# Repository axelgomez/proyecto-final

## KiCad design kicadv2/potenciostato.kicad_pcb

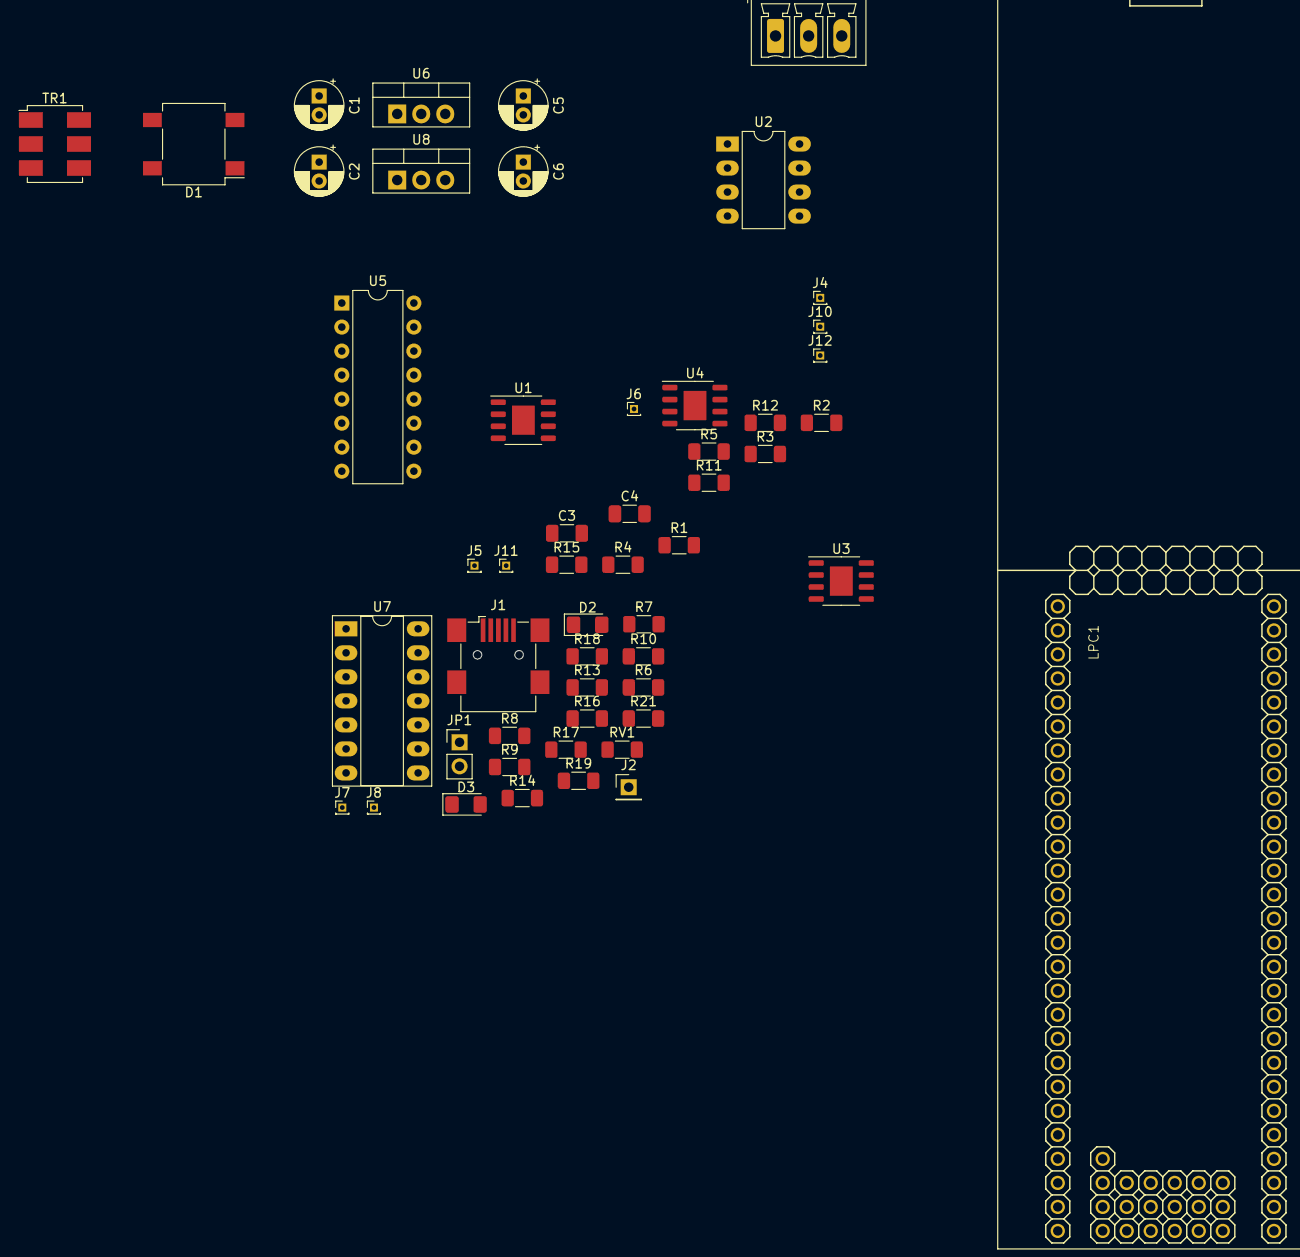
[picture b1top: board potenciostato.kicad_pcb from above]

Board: 2 copper layers, 52 parts (0 on the bottom side), 42 nets, no tracks yet.

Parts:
C1, C2, C5, C6: 10uF; CP_Radial_D5.0mm_P2.00mm
C3, C4: 100nF; C_1206_3216Metric_Pad1.33x1.80mm_HandSolder
D1: D_Bridge_+-AA; Diode_Bridge_Vishay_DFS
D2, D3: 1N4007; D_1206_3216Metric_Pad1.42x1.75mm_HandSolder
J1: USB_B_Micro; USB_Mini-B_Wuerth_65100516121_Horizontal
J2: test_DAC; PinHeader_1x01_P2.54mm_Vertical
J3: Conn_01x03_Male; PhoenixContact_MCV_1,5_3-G-3.5_1x03_P3.50mm_Vertical
J4, J7: test_I; PinHeader_1x01_P1.00mm_Vertical
J5, J8: test_V; PinHeader_1x01_P1.00mm_Vertical
J6: test_DAC; PinHeader_1x01_P1.00mm_Vertical
J10, J11, J12: test_GND; PinHeader_1x01_P1.00mm_Vertical
JP1: alimentacion_lpc; PinHeader_1x02_P2.54mm_Vertical
LPC1: LPCXPRESSO_LPC1769
R1, R10, R21: 1K; R_1206_3216Metric_Pad1.30x1.75mm_HandSolder
R2, R3, R11: 100K; R_1206_3216Metric_Pad1.30x1.75mm_HandSolder
R4, R6, R7, R8, R9, R14, R15, R18: 10K; R_1206_3216Metric_Pad1.30x1.75mm_HandSolder
R5: 6K8; R_1206_3216Metric_Pad1.30x1.75mm_HandSolder
R12, R17: 4K7; R_1206_3216Metric_Pad1.30x1.75mm_HandSolder
R13, R16, R19: 5K6; R_1206_3216Metric_Pad1.30x1.75mm_HandSolder
RV1: 10K; R_1206_3216Metric_Pad1.30x1.75mm_HandSolder
TR1: ADT2-71T; Mini-Circuits_CD637_H5.23mm
U1, U3, U4: OP77; HSOP-8-1EP_3.9x4.9mm_P1.27mm_EP2.41x3.1mm
U2: TL082; DIP-8_W7.62mm_LongPads
U5: 4316; DIP-16_W7.62mm
U6: L7805; TO-220-3_Vertical
U7: TL064; DIP-14_W7.62mm_Socket_LongPads
U8: L7905; TO-220-3_Vertical

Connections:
+5V: C5.1, JP1.1, R16.2, U1.7, U2.8, U3.7, U4.7, U5.16, U6.3, U7.4
-5V: C6.2, U1.4, U2.4, U3.4, U4.4, U5.9, U7.11, U8.3
/salida_dac/I_IN: J4.1, R14.2, U1.6, U5.2, U5.3, U5.11, U5.12
/salida_dac/VIN: J6.1, R2.2, R13.1, U7.1
/salida_dac/VOffset: R7.2, R8.1, R10.1, U7.13, U7.14
/salida_dac/V_IN: J5.1, R21.2, U2.6, U2.7
/salida_dac/gan_x0.1: LPC1.49, U5.15
/salida_dac/gan_x1: LPC1.47, U5.5
/salida_dac/gan_x5: LPC1.48, U5.6
/salida_dac/gan_x10: LPC1.50, U5.14
GND: C1.2, C2.1, C3.2, C4.1, C5.2, C6.1, D3.1, J1.5, J1.6, J10.1, J11.1, J12.1, LPC1.1, LPC1.54, R19.1, TR1.5, U1.3, U3.3, U4.3, U5.7, U5.8, U6.2, U8.1
unnamed: C1.1, C3.1, D1.1, U6.1
unnamed: C2.2, C4.2, D1.2, U8.2
unnamed: D1.3, TR1.4
unnamed: D1.4, TR1.6
unnamed: D2.1, D3.2
unnamed: D2.2, R16.1, R17.2
unnamed: J1.2, LPC1.36
unnamed: J1.3, LPC1.37
unnamed: J2.1, LPC1.18, R6.2
unnamed: J3.1, R5.1, U4.2
unnamed: J3.2, U2.3
unnamed: J3.3, U3.6
unnamed: J7.1, LPC1.15, R9.2, U7.8
unnamed: J8.1, LPC1.16, R18.2, U7.7
unnamed: JP1.2, LPC1.2
unnamed: R1.1, R4.2, R11.1, R12.1, R15.1, U1.2
unnamed: R1.2, U5.1
unnamed: R2.1, R3.1, U3.2
unnamed: R3.2, U2.1, U2.2, U2.5
unnamed: R4.1, R5.2, U4.6
unnamed: R7.1, U7.3
unnamed: R8.2, U7.10
unnamed: R10.2, U7.5
unnamed: R11.2, U5.13
unnamed: R12.2, U5.10
unnamed: R6.1, R13.2, U7.2
unnamed: R9.1, R14.1, U7.9
unnamed: R15.2, U5.4
unnamed: R17.1, RV1.1
unnamed: R18.1, R21.1, U7.6
unnamed: RV1.2, U7.12

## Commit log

2022-10-08 se agregan huellas smd
